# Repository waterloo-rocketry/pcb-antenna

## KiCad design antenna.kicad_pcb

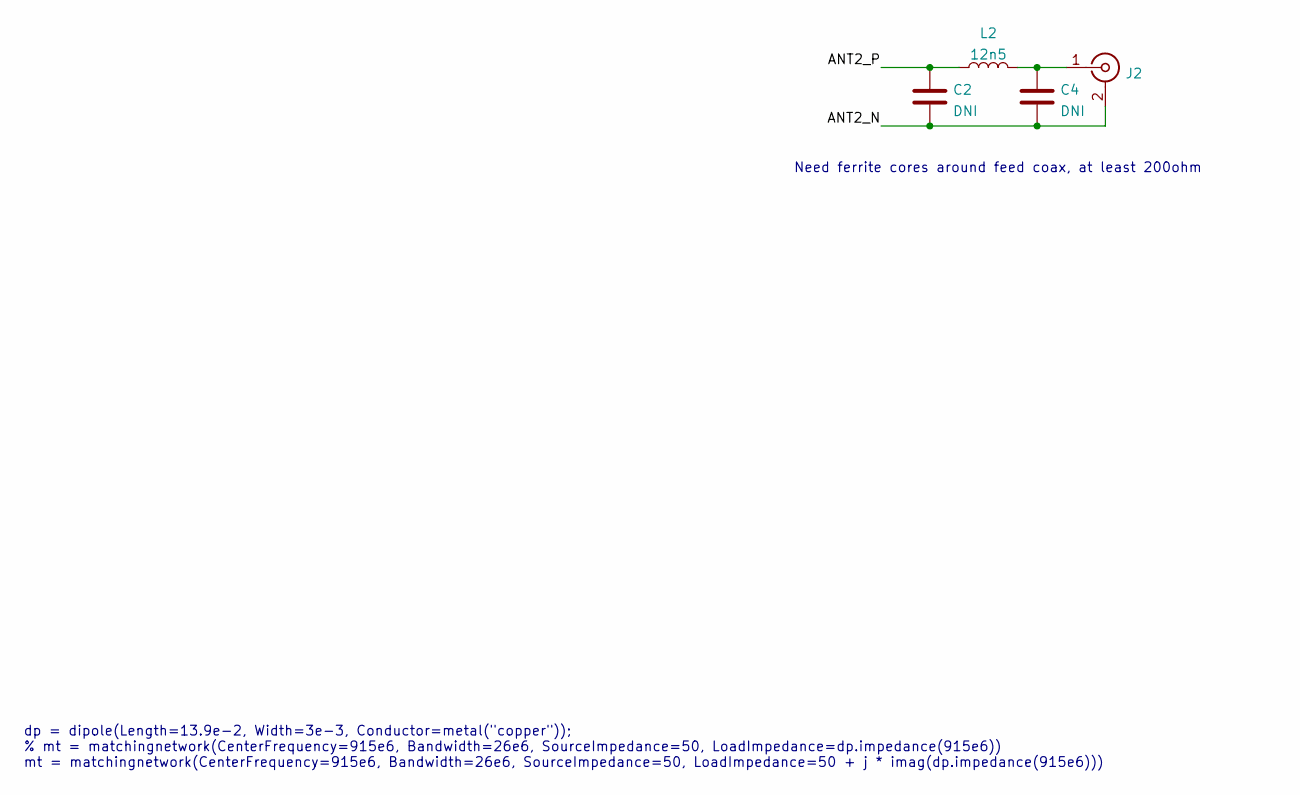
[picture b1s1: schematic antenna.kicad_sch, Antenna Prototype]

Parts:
C2, C4: DNI; C_0603_1608Metric_Pad1.08x0.95mm_HandSolder
J2: Conn_Coaxial; SMB_Jack_Vertical
L2: 12n5; L_0603_1608Metric_Pad1.05x0.95mm_HandSolder

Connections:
/ANT2_N: C2.2, C4.2, J2.2 (Ext)
/ANT2_P: C2.1, L2.1
unnamed: C4.1, J2.1 (In), L2.2

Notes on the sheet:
dp = dipole(Length=13.9e-2, Width=3e-3, Conductor=metal("copper")); % mt = matchingnetwork(CenterFrequency=915e6, Bandwidth=26e6, SourceImpedance=50, LoadImpedance=dp.impedance(915e6)) mt = matchingnetwork(CenterFrequency=915e6, Bandwidth=26e6, SourceImpedance=50, LoadImpedance=50 + j * imag(dp.imp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
Need ferrite cores around feed coax, at least 200ohm

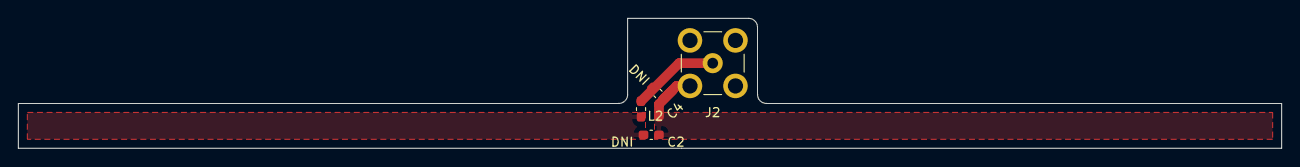
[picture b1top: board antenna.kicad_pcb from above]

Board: 2 copper layers, 141.0 x 14.5 mm, 4 parts (0 on the bottom side), 3 nets.

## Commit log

2022-11-12 pcb dipole antenna prototype
2022-11-12 Edit silkscreen and generate gerbers
2023-03-08 remove mounting points
2025-08-03 Made Single Antenna
